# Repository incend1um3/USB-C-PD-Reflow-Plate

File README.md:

<h1 align="center">
	USB-C PD Reflow Plate
	<br />
	<br />
	
	<br />
</h1>

<h4 align="center">
A DIY PCB Reflow Plate. Accepts 300W from a DC power source, or 110W from USB PD.
</h4>

<div align="center">

</div>

<p align="center">
  <a href="#key-features">Key Features</a> •
  <a href="#hardware">Hardware</a> •
  <a href="#building-and-flashing-the-firmware">Building and Flashing</a> •
  <a href="#license">License</a>
</p>

## Key Features

- **Split design** that allows you to manufacture the heater PCB using aluminum
- Accepts **USB-C PD (up to 110W)** or **DC supply (up to 300W)**
- **STM32G431KBT6 microcontroller** with support for flashing over USB and SWD
- **1.3" OLED display** for selecting alloys and showing progress
- **40 KHz PWM power delivery** to the heating element + a **970μF capacitor bank** to keep the average current under power supply limits

## Motivation

I started this project because existing designs had some flaws I disliked such as:

- No USB-C PD support
- Using obsolete Atmega chips that are too expensive for what they offer
- Not being powerful enough or requiring AC voltages which I don't want to mess around with
- Putting the electronics and heating elements on the same FR-4 PCB, making the longevity of the board questionable

This project is intended to address all these issues.

## Hardware

The hardware is split into two separate PCBs - a controller board and the heating element. This allows you to manufacture the heating element using aluminium to increase its longevity.

### Controller Board

#### Schematic

#### PCB

The controller PCB uses a 4 layer SIGNAL-GND-PWR-SIGNAL stackup. It measures under 100x50 mm, so you can get it manufactured for cheap at JLCPCB. 2x 470μF aluminum polymer capacitors are used to keep the average current within limits and smooth out the power supply.

### Heating Element

The traces are generated using the [Heater Generator Plugin](https://github.com/steltze/KiCad-Heater-Generator-Plugin), which uses the Hilbert Space Filling Curve to generate traces in a given bounding box.

The calculated resistance at 20°C is approximately 2.68Ω. The actual resistance after manufacturing can vary, but slight differences should not be a problem as long as the firmware is updated with the new value.

## Chassis

The chassis is made in Fusion360 and is designed to be printed using SLS/MJF nylon at JLC3DP. It occupies a bounding box of 220x166x73 mm and a total volume of 179 cm³.

## Manufacturing

All files related to manufacturing can be found in the `production` folder.

### BOM

<details>
<summary>Click to Expand / Collapse</summary>
<br />

The list of PCB components can be found [here.](production/Reflow%20Plate%20Controller/BOM-Reflow%20Plate%20Controller.csv)

| Name | Comment | Price ($USD) | Link |
|------|---------|--------------|------|
| PCB Components | | $25.63 | production/Reflow Plate Controller/BOM-Reflow Plate Controller.csv |
| 1.3" SSD1315 OLED Display | | $2.43 | <https://www.aliexpress.com/item/1005008365029314.html> |
| Glass NTC Thermistor | Must be able to withstand at least 250C | $4.03 | <https://www.aliexpress.com/item/1005008996648273.html> |
| Kapton Tape | For attaching the thermistor to the heating element | $2.72 | <https://www.aliexpress.com/item/33036160119.html> |
| XT30 Female Connector | For connecting the controller to the heating element | $2.17 | <https://www.aliexpress.com/item/1005011848365155.html> |
| M3x12 PEEK Screws | PEEK material chosen for insulation | $4.90 | <https://www.aliexpress.com/item/1005009212510720.html> |
| M3 Ceramic Washers | For insulation | $10.07 | <https://www.aliexpress.com/item/1005006898159426.html> |
| M3x45 Stainless Steel Standoffs | For insulation and attaching the heating element to the chassis | $2.55 | <https://www.aliexpress.com/item/1005010143571846.html> |
| M3x8 Screws | For attaching the controller PCB to the chassis | $1.61 | <https://www.aliexpress.com/item/1005010666684312.html> |
| M3x5x5 Heat Set Inserts | | $1.28 | <https://www.aliexpress.com/item/1005010449185019.html> |
| JLCPCB (Controller Board) | | $7.00 | |
| JLCPCBA (Controller Board) | | $14.53 | |
| JLCPCB (Heating Element) | | $12.40 | |
| JLC3DP (SLS 1172Pro Nylon) | | $59.95 | |
| JLCPCB Shipping | | $16.17 | |
| JLC3DP Shipping | | $17.07 | |
| LCSC Shipping | | $14.80 | |
| **Total** | | **$200.00** | |

</details>

### JLC Cart

<details>
<summary>Click to Expand / Collapse</summary>
<br />

</details>

### Aliexpress Cart

<details>
<summary>Click to Expand / Collapse</summary>
<br />

</details>

## Assembly

Heat up your soldering iron to the appropriate temperature for your chassis material. Take a heat-set insert, place it on a hole, and slowly push it through using the iron until the tip of the insert is flat with the surrounding surface. Repeat for the remaining screw holes.

Now you can go ahead and attach the PCBs using standoffs and screws.

## Building and Flashing the Firmware

The firmware is written in Rust. To build it, install the [rust toolchain](https://rust-lang.org/tools/install/) then run the following commands to install all the required components.

```bash
rustup target add thumbv7em-none-eabihf
cargo install cargo-binstall
cargo binstall cargo-dfu probe-rs-tools
```

### Flash Over USB

Plug in the controller board to your computer while holding the BOOT0 button to put the microcontroller in DFU mode. Then run:

```bash
cargo dfu --release
```

### Flash Over SWD (ST-LINK)

Connect your ST-LINK to the controller board using the SWD headers, then run:

```bash
cargo flash --release --chip STM32G431KB
```

## License

- `firmware/` is licensed under [GNU GPL v3](firmware/LICENSE)
- Rest of the repository is licensed under [CERN-OHL-S](LICENSE)

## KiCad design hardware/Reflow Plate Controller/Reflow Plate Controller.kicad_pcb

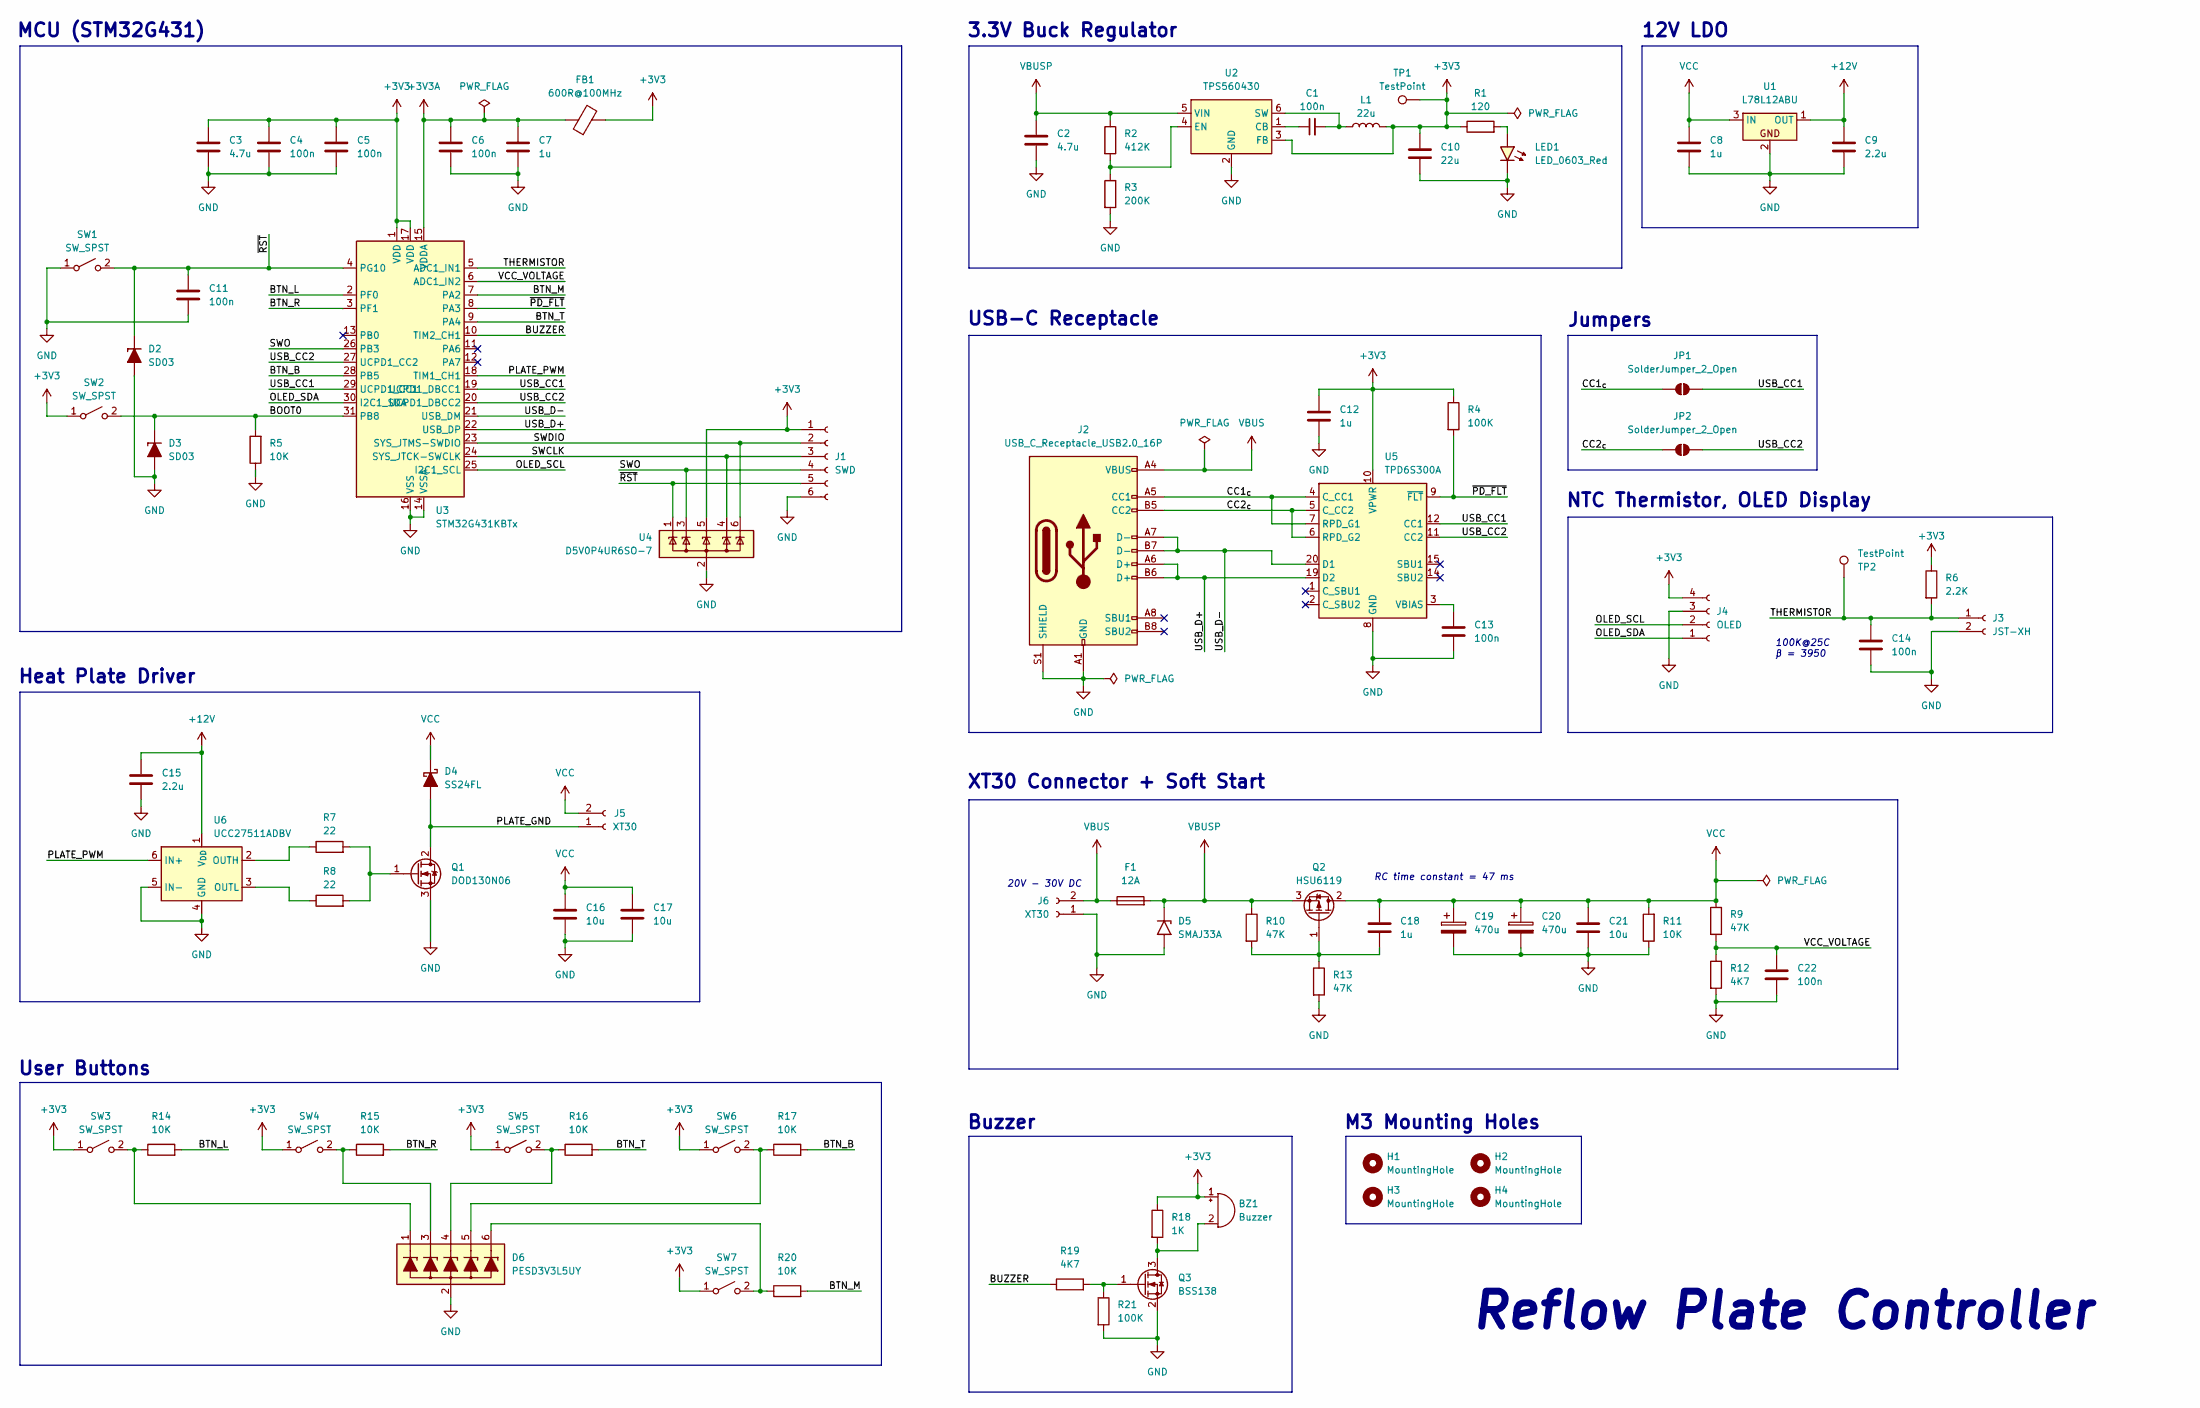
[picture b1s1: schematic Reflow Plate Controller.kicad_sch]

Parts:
BZ1: Buzzer; Buzzer_TDK_PS1240P02BT_D12.2mm_H6.5mm
C1, C4, C5, C6, C11, C13, C14, C22: 100n; C_0603_1608Metric_Pad1.08x0.95mm_HandSolder
C2: 4.7u; C_1206_3216Metric_Pad1.33x1.80mm_HandSolder
C3: 4.7u; C_0603_1608Metric_Pad1.08x0.95mm_HandSolder
C7, C12: 1u; C_0603_1608Metric_Pad1.08x0.95mm_HandSolder
C8, C18: 1u; C_0805_2012Metric_Pad1.18x1.45mm_HandSolder
C9, C15: 2.2u; C_0805_2012Metric_Pad1.18x1.45mm_HandSolder
C10: 22u; C_0603_1608Metric_Pad1.08x0.95mm_HandSolder
C16, C17, C21: 10u; C_1210_3225Metric_Pad1.33x2.70mm_HandSolder
C19, C20: 470u; CP_Radial_D10.0mm_P5.00mm
D2, D3: SD03; D_SOD-323_HandSoldering
D4: SS24FL; D_SOD-123F
D5: SMAJ33A; D_SMA
D6: PESD3V3L5UY; SOT-363_SC-70-6
F1: 12A; Fuse_2512_6332Metric_Pad1.52x3.35mm_HandSolder
FB1: 600R@100MHz; L_0603_1608Metric_Pad1.05x0.95mm_HandSolder
H1, H2, H3, H4: MountingHole; MountingHole_3.2mm_M3_Pad
J1: SWD; PinHeader_1x06_P2.54mm_Vertical
J2: USB_C_Receptacle_USB2.0_16P; USB_C_Receptacle_GCT_USB4105-xx-A_16P_TopMnt_Horizontal
J3: JST-XH; JST_XH_S2B-XH-A_1x02_P2.50mm_Horizontal
J4: OLED; PinSocket_1x04_P2.54mm_Vertical
J5, J6: XT30; AMASS_XT30PW-F_1x02_P2.50mm_Horizontal
JP1, JP2: SolderJumper_2_Open; SolderJumper-2_P1.3mm_Open_TrianglePad1.0x1.5mm
L1: 22u; L_1812_4532Metric_Pad1.30x3.40mm_HandSolder
LED1: LED_0603_Red; LED_0603_1608Metric
Q1: DOD130N06; TO-252-2
Q2: HSU6119; TO-252-2
Q3: BSS138; SOT-23
R1: 120; R_0603_1608Metric_Pad0.98x0.95mm_HandSolder
R2: 412K; R_0603_1608Metric_Pad0.98x0.95mm_HandSolder
R3: 200K; R_0603_1608Metric_Pad0.98x0.95mm_HandSolder
R4, R21: 100K; R_0603_1608Metric_Pad0.98x0.95mm_HandSolder
R5, R11, R14, R15, R16, R17, R20: 10K; R_0603_1608Metric_Pad0.98x0.95mm_HandSolder
R6: 2.2K; R_0603_1608Metric_Pad0.98x0.95mm_HandSolder
R7, R8: 22; R_0603_1608Metric_Pad0.98x0.95mm_HandSolder
R9, R10, R13: 47K; R_0603_1608Metric_Pad0.98x0.95mm_HandSolder
R12, R19: 4K7; R_0603_1608Metric_Pad0.98x0.95mm_HandSolder
R18: 1K; R_0603_1608Metric_Pad0.98x0.95mm_HandSolder
SW1, SW2, SW3, SW4, SW5, SW6, SW7: SW_SPST; SW_SPST_PTS647_Sx38
TP1, TP2: TestPoint; TestPoint_Pad_D1.0mm
U1: L78L12ABU; SOT-89-3
U2: TPS560430; SOT-23-6
U3: STM32G431KBTx; LQFP-32_7x7mm_P0.8mm
U4: D5V0P4UR6SO-7; SOT-23-6
U5: TPD6S300A; WQFN-20-1EP_3x3mm_P0.4mm_EP1.7x1.7mm_ThermalVias
U6: UCC27511ADBV; SOT-23-6

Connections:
+3V3: BZ1.1 (+), C3.1, C4.1, C5.1, C10.1, C12.1, FB1.2, J1.1, J4.4, L1.2, R1.1, R4.1, R6.1, R18.1, SW2.1 (A), SW3.1 (A), SW4.1 (A), SW5.1 (A), SW6.1 (A), SW7.1 (A), TP1.1 (1_1), U2.3 (FB), U3.1 (VDD), U3.17 (VDD), U4.5, U5.10 (VPWR)
+3V3A: C6.1, C7.1, FB1.1, U3.15 (VDDA)
+12V: C9.1, C15.1, U1.1 (OUT), U6.1 (V_{DD})
/BOOT0: D3.1, R5.2, SW2.2 (B), U3.31 (PB8)
/BTN_B: R17.2, U3.28 (PB5)
/BTN_L: R14.2, U3.2 (PF0)
/BTN_M: R20.2, U3.7 (PA2)
/BTN_R: R15.2, U3.3 (PF1)
/BTN_T: R16.2, U3.9 (PA4)
/BUZZER: R19.1, U3.10 (TIM2_CH1)
/CC1_{c}: J2.A5 (CC1), JP1.1 (A), U5.4 (C_CC1), U5.7 (RPD_G1)
/CC2_{c}: J2.B5 (CC2), JP2.1 (A), U5.5 (C_CC2), U5.6 (RPD_G2)
/OLED_SCL: J4.2, U3.25 (I2C1_SCL)
/OLED_SDA: J4.1, U3.30 (I2C1_SDA)
/PLATE_GND: D4.2 (A), J5.1, Q1.2 (D)
/PLATE_PWM: U3.18 (TIM1_CH1), U6.6 (IN+)
/SWCLK: J1.3, U3.24 (SYS_JTCK-SWCLK), U4.4
/SWDIO: J1.2, U3.23 (SYS_JTMS-SWDIO), U4.6
/SWO: J1.4, U3.26 (PB3), U4.3
/THERMISTOR: C14.1, J3.1, R6.2, TP2.1 (1_1), U3.5 (ADC1_IN1)
/USB_CC1: JP1.2 (B), U3.19 (UCPD1_DBCC1), U3.29 (UCPD1_CC1), U5.12 (CC1)
/USB_CC2: JP2.2 (B), U3.20 (UCPD1_DBCC2), U3.27 (UCPD1_CC2), U5.11 (CC2)
/USB_D+: J2.A6 (D+), J2.B6 (D+), U3.22 (USB_DP), U5.19 (D2)
/USB_D-: J2.A7 (D-), J2.B7 (D-), U3.21 (USB_DM), U5.20 (D1)
/VCC_VOLTAGE: C22.1, R9.2, R12.1, U3.6 (ADC1_IN2)
/~PD_FLT: R4.2, U3.8 (PA3), U5.9 (~FLT)
/~RST: C11.1, D2.1, J1.5, SW1.2 (B), U3.4 (PG10), U4.1
GND: C2.2, C3.2, C4.2, C5.2, C6.2, C7.2, C8.2, C9.2, C10.2, C11.2, C12.2, C13.2, C14.2, C15.2, C16.2, C17.2, C19.2, C20.2, C21.2, C22.2, D2.2, D3.2, D5.2 (A2), D6.2 (VN), J1.6, J2.A1 (GND), J2.A12 (GND), J2.B1 (GND), J2.B12 (GND), J2.S1 (SHIELD), J3.2, J4.3, J6.1, LED1.1 (K), Q1.3 (S), Q3.2 (S), R3.2, R5.1, R11.1, R12.2, R13.2, R21.2, SW1.1 (A), U1.2, U2.2 (GND), U3.14 (VSSA), U3.16 (VSS), U3.32 (VSS), U4.2, U5.8 (GND), U5.13 (GND), U5.16 (GND), U5.17 (GND), U5.18 (GND), U5.21 (GND), U6.4 (GND), U6.5 (IN-)
unnamed: BZ1.2 (-), Q3.3 (D), R18.2
unnamed: D6.1 (L1), R14.1, SW3.2 (B)
unnamed: D6.3 (L2), R15.1, SW4.2 (B)
unnamed: D6.4 (L3), R16.1, SW5.2 (B)
unnamed: D6.5 (L4), R17.1, SW6.2 (B)
unnamed: D6.6 (L5), R20.1, SW7.2 (B)
unnamed: LED1.2 (A), R1.2
unnamed: Q1.1 (G), R7.2, R8.2
unnamed: C18.2, Q2.1 (G), R10.2, R13.1
unnamed: Q3.1 (G), R19.2, R21.1
unnamed: C1.1, U2.1 (CB)
unnamed: R2.2, R3.1, U2.4 (EN)
unnamed: C1.2, L1.1, U2.6 (SW)
unnamed: C13.1, U5.3 (VBIAS)
unnamed: R7.1, U6.2 (OUTH)
unnamed: R8.1, U6.3 (OUTL)
VBUS: F1.1, J2.A4 (VBUS), J2.A9 (VBUS), J2.B4 (VBUS), J2.B9 (VBUS), J6.2
VBUSP: C2.1, D5.1 (A1), F1.2, Q2.3 (S), R2.1, R10.1, U2.5 (VIN)
VCC: C8.1, C16.1, C17.1, C18.1, C19.1, C20.1, C21.1, D4.1 (K), J5.2, Q2.2 (D), R9.1, R11.2, U1.3 (IN)

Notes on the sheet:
Heat Plate Driver
Jumpers
3.3V Buck Regulator
Buzzer
RC time constant = 47 ms
User Buttons
M3 Mounting Holes
NTC Thermistor, OLED Display
USB-C Receptacle
Reflow Plate Controller
20V - 30V DC
XT30 Connector + Soft Start
MCU (STM32G431)
12V LDO
100K@25C β = 3950

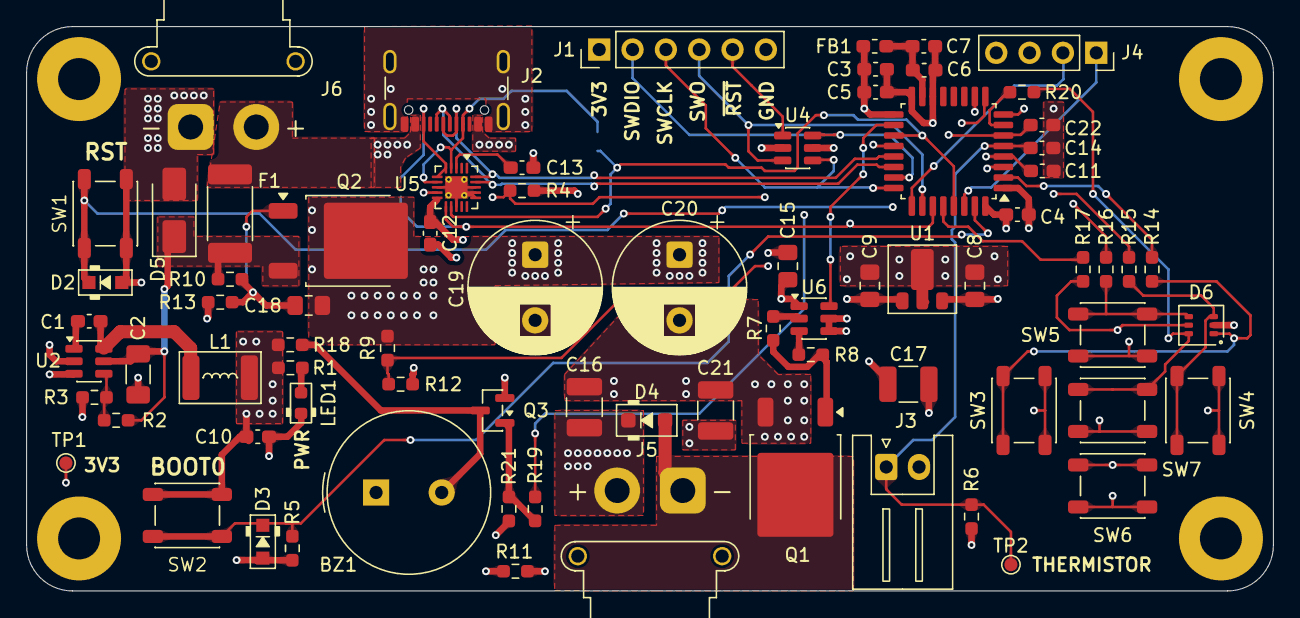
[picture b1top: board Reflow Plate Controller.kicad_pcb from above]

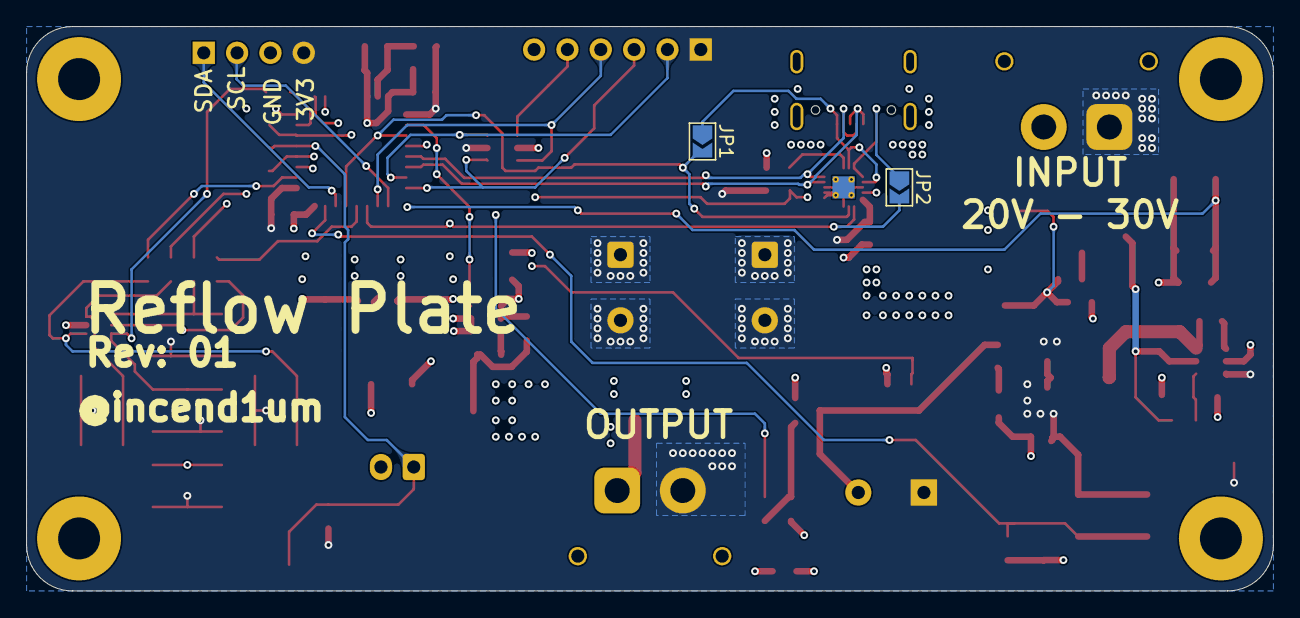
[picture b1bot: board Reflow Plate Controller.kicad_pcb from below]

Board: 4 copper layers, 95.0 x 43.0 mm, 83 parts (2 on the bottom side), 47 nets.

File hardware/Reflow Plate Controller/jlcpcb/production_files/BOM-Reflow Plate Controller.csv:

Comment,Designator,Footprint,LCSC,Quantity
100K,"R21,R4",R_0603_1608Metric_Pad0.98x0.95mm_HandSolder,C14675,2
100n,"C1,C11,C13,C14,C22,C4,C5,C6",C_0603_1608Metric_Pad1.08x0.95mm_HandSolder,C1591,8
10K,"R11,R14,R15,R16,R17,R20,R5",R_0603_1608Metric_Pad0.98x0.95mm_HandSolder,C98220,7
10u,"C16,C17,C21",C_1210_3225Metric_Pad1.33x2.70mm_HandSolder,C77102,3
120,R1,R_0603_1608Metric_Pad0.98x0.95mm_HandSolder,C22787,1
12A,F1,Fuse_2512_6332Metric_Pad1.52x3.35mm_HandSolder,C3014111,1
1K,R18,R_0603_1608Metric_Pad0.98x0.95mm_HandSolder,C21190,1
1u,C18,C_0805_2012Metric_Pad1.18x1.45mm_HandSolder,C15849,1
1u,"C12,C7",C_0603_1608Metric_Pad1.08x0.95mm_HandSolder,C1592,2
1u,C8,C_0805_2012Metric_Pad1.18x1.45mm_HandSolder,C28323,1
2.2K,R6,R_0603_1608Metric_Pad0.98x0.95mm_HandSolder,C4190,1
2.2u,"C15,C9",C_0805_2012Metric_Pad1.18x1.45mm_HandSolder,C377773,2
200K,R3,R_0603_1608Metric_Pad0.98x0.95mm_HandSolder,C25811,1
22,"R7,R8",R_0603_1608Metric_Pad0.98x0.95mm_HandSolder,C23345,2
22u,L1,L_1812_4532Metric_Pad1.30x3.40mm_HandSolder,C5788457,1
22u,C10,C_0603_1608Metric_Pad1.08x0.95mm_HandSolder,C59461,1
4.7u,C3,C_0603_1608Metric_Pad1.08x0.95mm_HandSolder,C1705,1
4.7u,C2,C_1206_3216Metric_Pad1.33x1.80mm_HandSolder,C51205,1
412K,R2,R_0603_1608Metric_Pad0.98x0.95mm_HandSolder,C2933219,1
470u,"C19,C20",CP_Radial_D10.0mm_P5.00mm,C51953324,2
47K,"R10,R13,R9",R_0603_1608Metric_Pad0.98x0.95mm_HandSolder,C25819,3
4K7,"R12,R19",R_0603_1608Metric_Pad0.98x0.95mm_HandSolder,C23162,2
600R@100MHz,FB1,L_0603_1608Metric_Pad1.05x0.95mm_HandSolder,C85833,1
BSS138,Q3,SOT-23,C40912,1
Buzzer,BZ1,Buzzer_TDK_PS1240P02BT_D12.2mm_H6.5mm,C76873,1
D5V0P4UR6SO-7,U4,SOT-23-6,C531179,1
HSU6119,Q2,TO-252-2,C53244079,1
JST-XH,J3,JST_XH_S2B-XH-A_1x02_P2.50mm_Horizontal,C163035,1
L78L12ABU,U1,SOT-89-3,C915681,1
LED_0603_Red,LED1,LED_0603_1608Metric,C965799,1
PESD3V3L5UY,D6,SOT-363_SC-70-6,C477992,1
SD03,"D2,D3",D_SOD-323_HandSoldering,C5369353,2
SMAJ33A,D5,D_SMA,C134981,1
SS24FL,D4,D_SOD-123F,C894433,1
STM32G431KBTx,U3,LQFP-32_7x7mm_P0.8mm,C529357,1
SW_SPST,"SW1,SW2,SW3,SW4,SW5,SW6,SW7",SW_SPST_PTS647_Sx38,C963225,7
TPD6S300A,U5,WQFN-20-1EP_3x3mm_P0.4mm_EP1.7x1.7mm_ThermalVias,C2876380,1
TPS560430,U2,SOT-23-6,C2071721,1
UCC27511ADBV,U6,SOT-23-6,C2676982,1
USB_C_Receptacle_USB2.0_16P,J2,USB_C_Receptacle_GCT_USB4105-xx-A_16P_TopMnt_Horizontal,C165948,1
XT30,"J5,J6",AMASS_XT30PW-F_1x02_P2.50mm_Horizontal,C2913282,2
DOD130N06,Q1,TO-252-2,,1

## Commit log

2026-04-02 Fix a few layout and component selection issues
    - Replace out-of-stock components
    - Remove some of the 100nF caps that are in parallel with a larger value
    - Swap PTVS3V3 -> SD03
    - Swap the PMOS to HSU6119 and the NMOS to DOD130N06 for lower Rds(on)
    - Slightly increase the copper area around the FETs
    - Reduce the soft-start duration to 47 ms
2026-04-06 Thicken walls and add gussets to reduce warping risks
2026-06-14 fix firmware
2026-06-14 update zone fills (gerbers had a short circuit)
